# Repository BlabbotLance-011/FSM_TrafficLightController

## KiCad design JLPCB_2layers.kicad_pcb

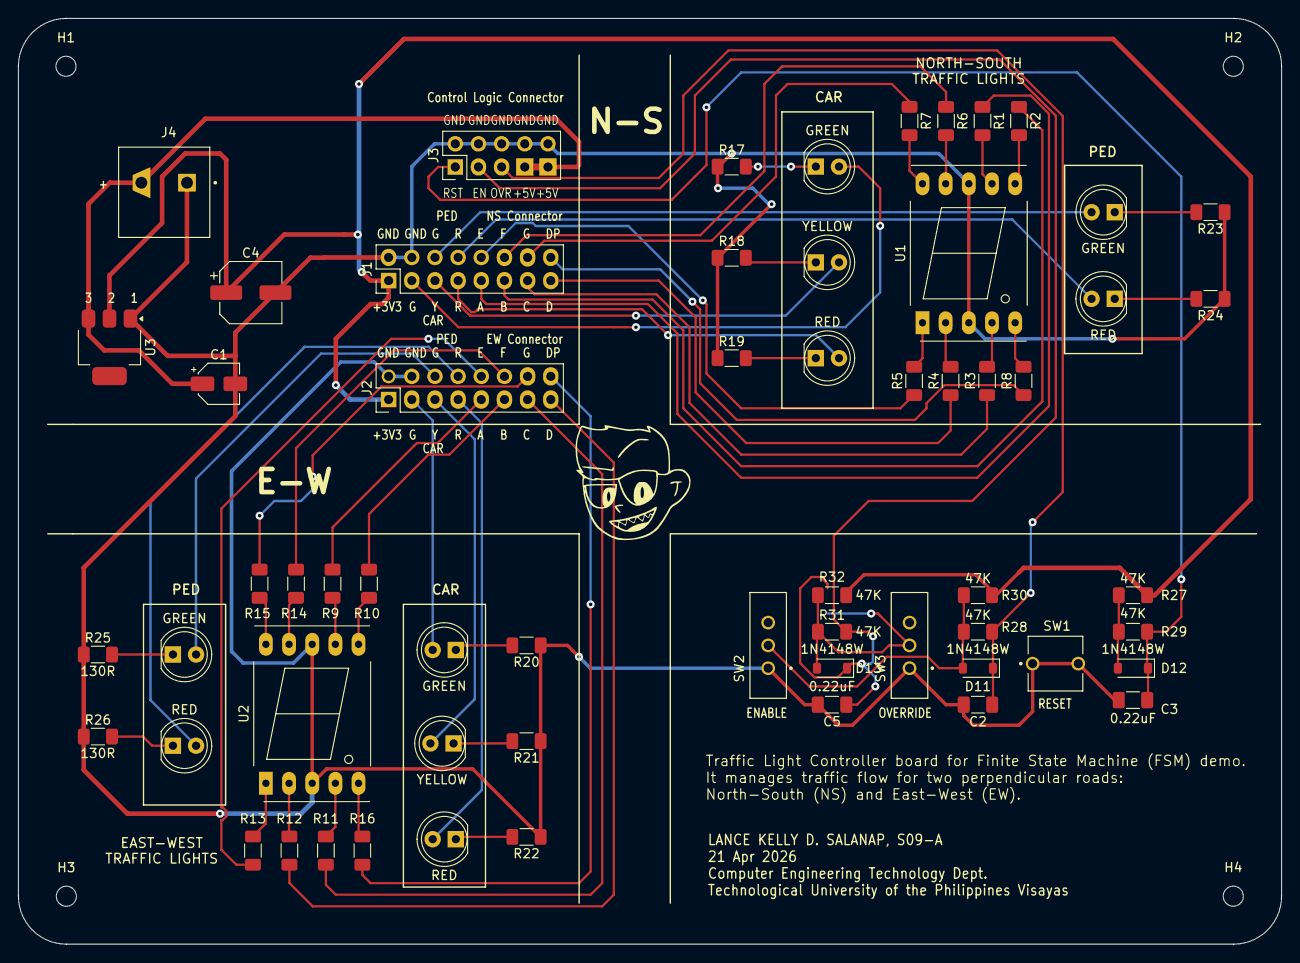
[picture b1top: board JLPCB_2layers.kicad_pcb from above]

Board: 2 copper layers, 138.5 x 101.5 mm, 64 parts (0 on the bottom side), 61 nets.

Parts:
C1: 10uF; CP_Elec_4x5.3
C2, C3, C5: 0.22uF; C_1206_3216Metric_Pad1.33x1.80mm_HandSolder
C4: 100uF; CP_Elec_6.3x5.8
D11, D12, D13: 1N4148W; D_SOD-123
GREEN: NSP_GRN; LED_D5.0mm
GREEN#2: EWC_GRN; LED_D5.0mm
GREEN#3: EWP_GRN; LED_D5.0mm
GREEN#4: NSC_GRN; LED_D5.0mm
H1, H2, H3, H4: MountingHole; MountingHole_2.2mm_M2
J1: NS Connector; PinHeader_2x08_P2.54mm_Vertical
J2: EW Connector; PinHeader_2x08_P2.54mm_Vertical
J3: Control Logic Connector; PinHeader_2x05_P2.54mm_Vertical
J4: +5V; Terminal_Block_5mm
R1, R2, R3, R4, R5, R6, R7, R8, R9, R10, R11, R12, R13, R14, R15, R16, R17, R18, R19, R20, R21, R22, R23, R24, R25, R26: 130R; R_1206_3216Metric_Pad1.30x1.75mm_HandSolder
R27, R28, R29, R30, R31, R32: 47K; R_1206_3216Metric_Pad1.30x1.75mm_HandSolder
RED: EWP_RED; LED_D5.0mm
RED#2: NSP_RED; LED_D5.0mm
RED#3: NSC_RED; LED_D5.0mm
RED#4: EWC_RED; LED_D5.0mm
SW1: RST; tact_switch_5mm
SW2: OVR; slide_switch_2.54mm
SW3: EN; slide_switch_2.54mm
U1, U2: SM420561N; 7SegmentLED_LTS6760_LTS6780
U3: LM1117DT-3.3; SOT-223
YELLOW: EWC_YLW; LED_D5.0mm
YELLOW#2: NSC_YLW; LED_D5.0mm

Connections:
/+3.3V: C4.1, J1.1, J2.1, R27.1, R30.1, R32.1, U3.2 (VO)
/+5V: C1.1, J3.7, J3.9, J4.2, U3.3 (VI)
/EN: C5.1, D13.1 (K), J3.3, R31.2
/EWC_GRN: GREEN#2.2 (A), J2.3
/EWC_RED: J2.7, RED#4.2 (A)
/EWC_YLW: J2.5, YELLOW.2 (A)
/EWP_GRN: GREEN#3.2 (A), J2.6
/EWP_RED: J2.8, RED.2 (A)
/EW_HEX_A: J2.9, R9.1
/EW_HEX_B: J2.11, R10.1
/EW_HEX_C: J2.13, R11.1
/EW_HEX_D: J2.15, R12.1
/EW_HEX_DP: J2.16, R16.1
/EW_HEX_E: J2.10, R13.1
/EW_HEX_F: J2.12, R14.1
/EW_HEX_G: J2.14, R15.1
/NSC_GRN: GREEN#4.2 (A), J1.3
/NSC_RED: J1.7, RED#3.2 (A)
/NSC_YLW: J1.5, YELLOW#2.2 (A)
/NSP_GRN: GREEN.2 (A), J1.6
/NSP_RED: J1.8, RED#2.2 (A)
/NS_HEX_A: J1.9, R1.1
/NS_HEX_B: J1.11, R2.1
/NS_HEX_C: J1.13, R3.1
/NS_HEX_D: J1.15, R4.1
/NS_HEX_DP: J1.16, R8.1
/NS_HEX_E: J1.10, R5.1
/NS_HEX_F: J1.12, R6.1
/NS_HEX_G: J1.14, R7.1
/OVR: C2.1, D11.1 (K), J3.5, R28.1
/RST: C3.1, D12.1 (K), J3.1, R29.2
GND: C1.2, C2.2, C3.2, C4.2, C5.2, J1.2, J1.4, J2.2, J2.4, J3.2, J3.4, J3.6, J3.8, J3.10, J4.1, R17.1, R18.1, R19.1, R20.1, R21.1, R22.1, R23.1, R24.1, R25.1, R26.1, SW1.1 (A), SW1.2 (A), SW2.1 (C), SW3.1 (C), U1.3 (CC), U1.8 (CC), U2.3 (CC), U2.8 (CC), U3.1 (GND)
unnamed: GREEN#4.1 (K), R17.2
unnamed: R18.2, YELLOW#2.1 (K)
unnamed: R19.2, RED#3.1 (K)
unnamed: GREEN#2.1 (K), R20.2
unnamed: R21.2, YELLOW.1 (K)
unnamed: R22.2, RED#4.1 (K)
unnamed: GREEN.1 (K), R23.2
unnamed: R24.2, RED#2.1 (K)
unnamed: GREEN#3.1 (K), R25.2
unnamed: R26.2, RED.1 (K)
unnamed: D11.2 (A), R28.2, R30.2, SW2.2 (B)
unnamed: D12.2 (A), R27.2, R29.1
unnamed: D13.2 (A), R31.1, R32.2, SW3.2 (B)
unnamed: R1.2, U1.7 (A)
unnamed: R2.2, U1.6 (B)
unnamed: R3.2, U1.4 (C)
unnamed: R4.2, U1.2 (D)
unnamed: R8.2, U1.5 (DP)
unnamed: R5.2, U1.1 (E)
unnamed: R6.2, U1.9 (F)
unnamed: R7.2, U1.10 (G)
unnamed: R9.2, U2.7 (A)
unnamed: R10.2, U2.6 (B)
unnamed: R11.2, U2.4 (C)
unnamed: R12.2, U2.2 (D)
unnamed: R16.2, U2.5 (DP)
unnamed: R13.2, U2.1 (E)
unnamed: R14.2, U2.9 (F)
unnamed: R15.2, U2.10 (G)

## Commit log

2026-04-20 Add files
2026-04-20 Do schematic files (part 1)
2026-04-20 Finalize Traffic Light Schematics
2026-04-20 Finalized Schematic Diagram
2026-04-20 No error on schematic update
2026-04-20 Starting up PCB
2026-04-21 Finalized and finished PCB
2026-04-21 Finishing up and finalize PCB
